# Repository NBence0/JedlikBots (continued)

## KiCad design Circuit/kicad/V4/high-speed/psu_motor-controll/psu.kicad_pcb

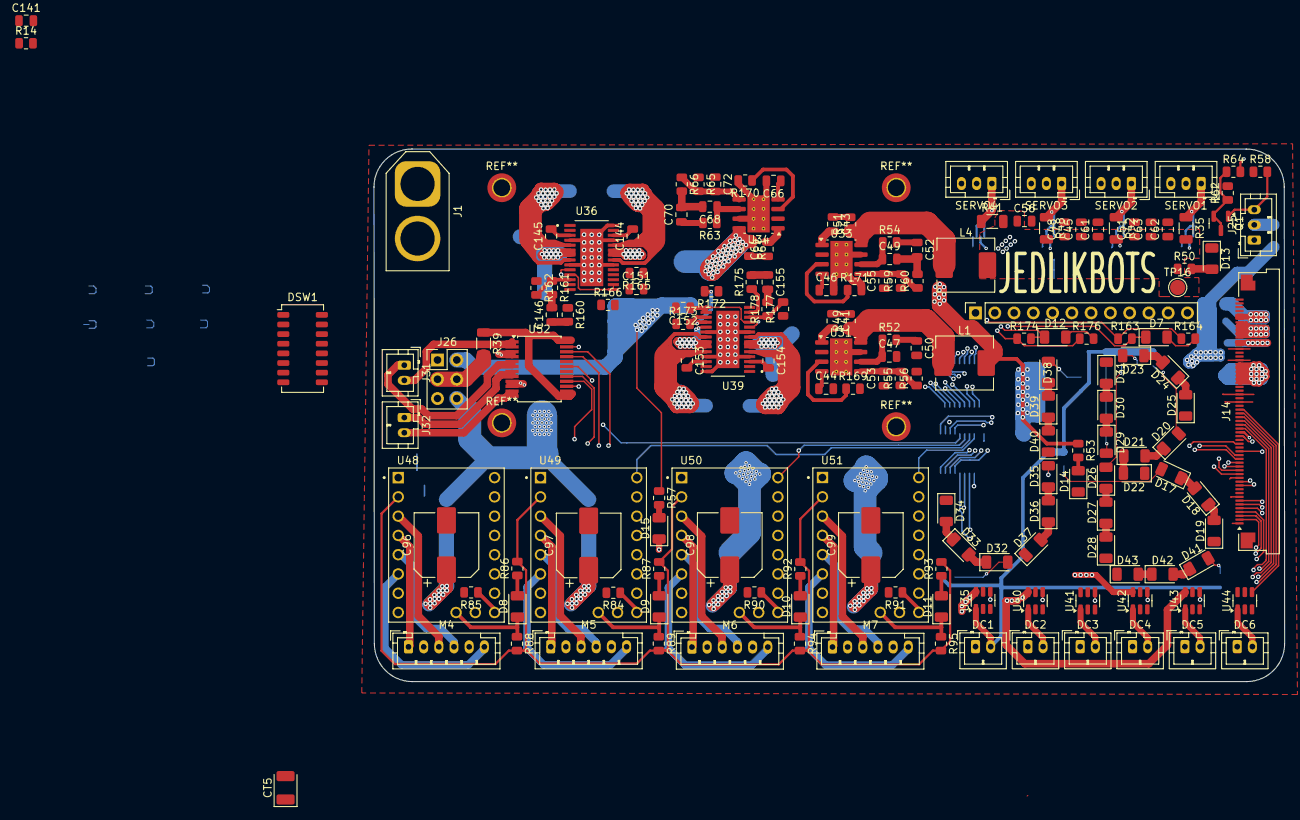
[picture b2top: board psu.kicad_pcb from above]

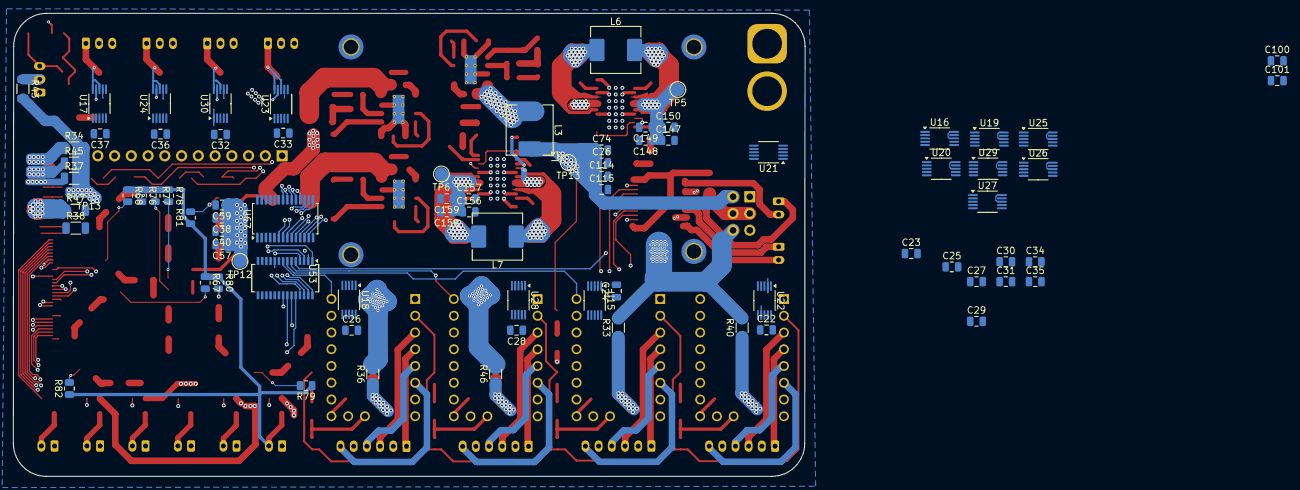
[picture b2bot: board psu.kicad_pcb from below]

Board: 6 copper layers, 120.0 x 70.2 mm, 245 parts (78 on the bottom side), 202 nets.

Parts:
C22, C23, C24, C25, C26, C27, C28, C29, C30, C31, C32, C33, C34, C35, C36, C37, C100, C101, C141: 1uf; C_0805_2012Metric
C38, C40, C45, C48, C51, C56, C57, C59, C61, C62, C63, C74, C76, C114, C115, C147, C148, C149, C150, C151, C152, C156, C157, C158, C159: 4,7uf; C_0805_2012Metric
C41, C43, C44, C46, C64, C66, C144, C145, C153, C154: 100n; C_0805_2012Metric
C47, C49, C53, C55, C68, C72: 68pf; C_0805_2012Metric
C50, C52, C70: 1.2nF; C_0805_2012Metric
C96, C97, C98, C99: 470uf; CP_Elec_8x10
C146, C155: 330pf; C_0805_2012Metric
CT5: 10uf; CP_EIA-3528-21_Kemet-B
D7, D8, D9, D10, D11, D12, D13, D14, D15, D17, D18, D19, D20, D21, D22, D23, D24, D25, D26, D27, D28, D29, D30, D31, D32, D33, D34, D35, D36, D37, D38, D39, D40, D41, D42, D43: LED; D_1206_3216Metric
DC1, DC2, DC3, DC4, DC5, DC6: Conn_01x02_Socket; JST_PH_B2B-PH-K_1x02_P2.00mm_Vertical
DSW1: SW_DIP_x08; SW_DIP_SPSTx08_Slide_Copal_CHS-08A_W5.08mm_P1.27mm_JPin
J1: XT60-M; AMASS_XT60-M_1x02_P7.20mm_Vertical
J14: Conn_01x60_MountingPin; Amphenol_F32Q-1A7x1-11060_1x60-1MP_P0.5mm_Horizontal
J16: Conn_01x12; PinSocket_1x12_P2.54mm_Vertical
J25: Conn_01x03_Pin; JST_PH_B3B-PH-K_1x03_P2.00mm_Vertical
J26: Conn_02x03_Counter_Clockwise; PinHeader_2x03_P2.54mm_Vertical
J31, J32: Conn_01x02_Pin; JST_PH_B2B-PH-K_1x02_P2.00mm_Vertical
L1, L3, L4, L6, L7: HCM0703-3R3-R; L_KOHERelec_MDA7030
M4, M5, M6, M7: Stepper_Motor_unipolar_6pin; JST_PH_B6B-PH-K_1x06_P2.00mm_Vertical
Q1: bss138; SOT-23
R14, R84, R85, R88, R89, R90, R91, R94, R95, R163, R174: 10k; R_0805_2012Metric
R33, R34, R35, R36, R37, R38, R39, R40, R41, R42, R43, R45, R46, R47, R48: 0.025Ω; R_1206_3216Metric
R49, R51, R61: 10R; R_0805_2012Metric
R50: 1k; R_0805_2012Metric
R52, R54, R63: 12K 1%; R_0805_2012Metric
R53: 100; R_0805_2012Metric
R55: 105k; R_0805_2012Metric
R56, R60, R66: 33k; R_0805_2012Metric
R57, R86, R87, R92, R93: 330; R_0805_2012Metric
R58, R62, R64: 100R; R_0805_2012Metric
R59: 210k; R_0805_2012Metric
R65: 178k; R_0805_2012Metric
R67, R68, R76, R77, R78, R79, R80, R81, R82: R_LED; R_0805_2012Metric
R160, R175: 154k; R_0805_2012Metric
R161, R178: 36k; R_0805_2012Metric
R162, R177: 510k; R_0805_2012Metric
R164, R176: 2,2k; R_0805_2012Metric
R165, R173: 34,8k; R_0805_2012Metric
R166, R169, R170, R171, R172: 47k; R_0805_2012Metric
SERVO1, SERVO2, SERVO3, SERVO4: Conn_01x03_Socket; JST_PH_B3B-PH-K_1x03_P2.00mm_Vertical
TP5, TP6, TP12, TP13, TP16: TestPoint; TestPoint_Pad_D2.0mm
U15, U16, U17, U18, U19, U20, U21, U22, U23, U24, U25, U26, U27, U28, U29, U30: INA226; VSSOP-10_3x3mm_P0.5mm
U31, U33, U34: AP64501SP-13; SOIC-8-1EP_3.9x4.9mm_P1.27mm_EP2.95x4.9mm_Mask2.71x3.4mm_Th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
U35, U40, U41, U42, U43, U44: AP22815AWU; SOT-23-6
U36, U39: LTC3119EFE_PBF; SOP65P640X120-29N
U48, U49, U50, U51: TMC2240_SILENTSTEPSTICK; TMC2209
U52: TB6612FNG; SSOP-24_5.3x8.2mm_P0.65mm
U53: MCP23S17_SO; SSOP-28_3.9x9.9mm_P0.635mm
U67: PCA9685PW; TSSOP-28_4.4x9.7mm_P0.65mm

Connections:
3V3_M.2: J14.38, J14.39, J14.40, J14.41, J14.42, J14.43, R47.1, U29.8 (Vbus), U29.10 (Vin+)
3v3: C38.1, C40.1, C53.1, C57.1, C59.1, J26.1, L1.2, R38.2, R47.2, R53.1, R55.1, TP12.1, U20.9 (Vin-), U29.9 (Vin-)
5V1: C22.1, C23.2, C24.1, C25.2, C26.1, C27.2, C28.1, C29.2, C30.1, C31.2, C32.1, C33.2, C34.1, C35.2, C36.1, C37.2, J14.55, J14.56, R34.1, U15.6 (VS), U16.1 (A1), U16.2 (A0), U16.6 (VS), U16.8 (Vbus), U16.10 (Vin+), U17.6 (VS), U18.1 (A1), U18.6 (VS), U19.2 (A0), U19.6 (VS), U20.6 (VS), U21.1 (A1), U21.6 (VS), U22.6 (VS), U23.2 (A0), U23.6 (VS), U24.6 (VS), U25.6 (VS), U26.6 (VS), U27.1 (A1), U27.6 (VS), U28.2 (A0), U28.6 (VS), U29.6 (VS), U30.6 (VS), U41.6 (IN), U44.6 (IN)
5v: C72.1, C74.1, C76.1, C114.1, C115.1, DSW1.7, J26.2, L3.2, R34.2, R37.2, R43.2, R45.2, R57.1, R65.1, TP13.1, U16.9 (Vin-), U19.9 (Vin-), U25.9 (Vin-), U27.9 (Vin-)
/12v_1: C147.1, C148.1, C149.1, C150.1, J26.6, R33.2, R40.2, R162.1, R163.1, R164.1, TP5.1, U15.9 (Vin-), U22.9 (Vin-), U36.6 (PVOUT), U36.7 (PVOUT)
/12v_2: C156.1, C157.1, C158.1, C159.1, R36.2, R46.2, R174.1, R176.1, R177.1, TP6.1, U18.9 (Vin-), U28.9 (Vin-), U39.6 (PVOUT), U39.7 (PVOUT)
/INA226/-1000111: J26.3, J26.4, R39.2, U21.9 (Vin-)
/PSUs/3v3_enable: DSW1.15, R169.1, U31.3 (EN)
/PSUs/5v_enable: DSW1.14, R170.1, U34.3 (EN)
/PSUs/12v_v1_enable: DSW1.12, R166.2, U36.18 (RUN)
/PSUs/12v_v2_enable: DSW1.11, R172.2, U39.18 (RUN)
/PSUs/servo_enable: DSW1.13, R171.1, U33.3 (EN)
/SW_N: DSW1.1, J1.2 (POS)
/SW_P: DSW1.16, J1.1 (NEG)
/YD-ESP32-S3/4x tmc5161/M1_CS: U48.13 (Chip_select), U53.21 (GPA0)
/YD-ESP32-S3/4x tmc5161/M1_EN: R85.1, U48.16 (Enable), U53.1 (GPB0)
/YD-ESP32-S3/4x tmc5161/M2_CS: U50.13 (Chip_select), U53.22 (GPA1)
/YD-ESP32-S3/4x tmc5161/M2_EN: R90.1, U50.16 (Enable), U53.2 (GPB1)
/YD-ESP32-S3/4x tmc5161/M3_CS: U49.13 (Chip_select), U53.23 (GPA2)
/YD-ESP32-S3/4x tmc5161/M3_EN: R84.1, U49.16 (Enable), U53.3 (GPB2)
/YD-ESP32-S3/4x tmc5161/M4_CS: U51.13 (Chip_select), U53.24 (GPA3)
/YD-ESP32-S3/4x tmc5161/M4_EN: R91.1, U51.16 (Enable), U53.4 (GPB3)
/YD-ESP32-S3/H-bridge/AIN1: U52.21 (AIN1), U53.28 (GPA7)
/YD-ESP32-S3/H-bridge/AIN2: U52.22 (AIN2), U53.27 (GPA6)
/YD-ESP32-S3/H-bridge/BIN1: U52.17 (BIN1), U53.26 (GPA5)
/YD-ESP32-S3/H-bridge/BIN2: U52.16 (BIN2), U53.25 (GPA4)
/YD-ESP32-S3/I2C_SCL_sensors: J14.10, U67.27 (SDA)
/YD-ESP32-S3/I2C_SDA_sensors: J14.9, U67.26 (SCL)
/YD-ESP32-S3/I2C_devices/PCA9531PW/SM1_PWM: SERVO1.2, U67.6 (LED0)
/YD-ESP32-S3/I2C_devices/PCA9531PW/SM2_PWM: SERVO2.2, U67.7 (LED1)
/YD-ESP32-S3/I2C_devices/PCA9531PW/SM3_PWM: SERVO3.2, U67.8 (LED2)
/YD-ESP32-S3/I2C_devices/PCA9531PW/SM4_PWM: SERVO4.2, U67.9 (LED3)
/YD-ESP32-S3/M1_dir: U48.9 (DIR), U53.5 (GPB4)
/YD-ESP32-S3/M1_step: J14.17, U48.10 (STEP)
/YD-ESP32-S3/M2_dir: U50.9 (DIR), U53.6 (GPB5)
/YD-ESP32-S3/M2_step: J14.16, U50.10 (STEP)
/YD-ESP32-S3/M3_dir: U49.9 (DIR), U53.7 (GPB6)
/YD-ESP32-S3/M3_step: J14.15, U49.10 (STEP)
/YD-ESP32-S3/M4_dir: U51.9 (DIR), U53.8 (GPB7)
/YD-ESP32-S3/M4_step: J14.14, U51.10 (STEP)
/YD-ESP32-S3/MCP_RST: J14.20, U53.18 (~RESET)
/YD-ESP32-S3/PWMA: J14.19, U52.23 (PWMA)
/YD-ESP32-S3/PWMB: J14.18, U52.15 (PWMB)
/YD-ESP32-S3/SPI_2_CLK: J14.7, U53.12 (SCK)
/YD-ESP32-S3/SPI_2_MISO: J14.5, U53.14 (SO)
/YD-ESP32-S3/SPI_2_MOSI: J14.6, U53.13 (SI)
/YD-ESP32-S3/Shift_registers/JB_leds/+12V: DC1.2, R67.1, R68.1, R76.1, R77.1, R78.1, R79.1, R80.1, R81.1, R82.1, U35.1 (OUT)
/YD-ESP32-S3/TMC_MISO: J14.2, U48.11 (MISO), U49.11 (MISO), U50.11 (MISO), U51.11 (MISO)
/YD-ESP32-S3/TMC_MOSI: J14.4, U48.15 (MOSI), U49.15 (MOSI), U50.15 (MOSI), U51.15 (MOSI)
/YD-ESP32-S3/TMC_SPI_CLK: J14.3, U48.14 (Spi_clk), U49.14 (Spi_clk), U50.14 (Spi_clk), U51.14 (Spi_clk)
/servo: C45.1, C48.1, C51.1, C55.1, C56.1, C61.1, C62.1, C63.1, J26.5, L4.2, R35.2, R41.2, R42.2, R48.2, R50.1, R59.1, TP16.1, U17.9 (Vin-), U23.9 (Vin-), U24.9 (Vin-), U30.9 (Vin-)
B-B_2: J14.31, U44.4 (EN)
B-B_3: J14.30, U43.4 (EN)
B-B_4: J14.29, U42.4 (EN)
B-B_5: J14.28, U41.4 (EN)
B-B_6: J14.27, U40.4 (EN)
B-B_7: J14.26, U35.4 (EN)
ESP_3v3: C100.1, C101.1, C141.1, CT5.1, J14.36, J14.37, R38.1, R62.2, R86.2, R87.2, R88.2, R89.2, R92.2, R93.2, R94.2, R95.2, U20.8 (Vbus), U20.10 (Vin+), U40.6 (IN), U43.6 (IN), U48.2 (VIO/VDD), U49.2 (VIO/VDD), U50.2 (VIO/VDD), U51.2 (VIO/VDD), U52.20 (VCC), U53.9 (VDD), U67.2 (A1), U67.5 (A4), U67.24 (A5), U67.28 (VDD)
ESP_5v: J14.48, J14.49, R37.1, R58.1, U19.8 (Vbus), U19.10 (Vin+)
GND: C22.2, C23.1, C24.2, C25.1, C26.2, C27.1, C28.2, C29.1, C30.2, C31.1, C32.2, C33.1, C34.2, C35.1, C36.2, C37.1, C38.2, C40.2, C44.2, C45.2, C46.2, C47.2, C48.2, C49.2, C50.2, C51.2, C52.2, C56.2, C57.2, C59.2, C61.2, C62.2, C63.2, C66.2, C68.2, C70.2, C74.2, C76.2, C96.2, C97.2, C98.2, C99.2, C100.2, C101.2, C114.2, C115.2, C141.2, C147.2, C148.2, C149.2, C150.2, C151.2, C152.2, C156.2, C157.2, C158.2, C159.2, CT5.2, D13.1 (K), D14.1 (K), D15.1 (K), D19.1 (K), D22.1 (K), D25.1 (K), D28.1 (K), D31.1 (K), D34.1 (K), D37.1 (K), D40.1 (K), D43.1 (K), DC1.1, DC2.1, DC3.1, DC4.1, DC5.1, DC6.1, DSW1.9, J14.1, J14.8, J14.13, J14.33, J14.34, J14.35, J14.44, J14.45, J14.46, J14.47, J14.57, J14.58, J14.59, J14.60, J14.MP (MountPin), J25.1, R14.2, R56.2, R60.2, R66.2, R84.2, R85.2, R90.2, R91.2, R165.1, R166.1, R169.2, R170.2, R171.2, R172.1, R173.1, SERVO1.3, SERVO2.3, SERVO3.3, SERVO4.3, U15.1 (A1), U15.2 (A0), U15.7 (GND), U16.7 (GND), U17.7 (GND), U18.2 (A0), U18.7 (GND), U19.7 (GND), U20.7 (GND), U21.7 (GND), U22.2 (A0), U22.7 (GND), U23.7 (GND), U24.7 (GND), U25.2 (A0), U25.7 (GND), U26.1 (A1), U26.7 (GND), U27.7 (GND), U28.1 (A1), U28.7 (GND), U29.7 (GND), U30.1 (A1), U30.7 (GND), U31.7 (GND), U31.9 (EP), U33.7 (GND), U33.9 (EP), U34.7 (GND), U34.9 (EP), U35.2 (GND), U36.4 (PGND), U36.9 (PGND), U36.14 (SGND), U36.20 (PGND), U36.25 (PGND), U36.28 (PWM/SYNC), U36.29 (PGND), U39.4 (PGND), U39.9 (PGND), U39.14 (SGND), U39.20 (PGND), U39.25 (PGND), U39.28 (PWM/SYNC), U39.29 (PGND), U40.2 (GND), U41.2 (GND), U42.2 (GND), U43.2 (GND), U44.2 (GND), U48.1 (GND), U48.7 (GND), U49.1 (GND), U49.7 (GND), U50.1 (GND), U50.7 (GND), U51.1 (GND), U51.7 (GND), U52.3 (PGND1), U52.4 (PGND1), U52.9 (PGND2), U52.10 (PGND2), U52.18 (GND), U53.10 (VSS), U53.15 (A0), U53.16 (A1), U53.17 (A2), U67.1 (A0), U67.3 (A2), U67.4 (A3), U67.14 (VSS)
H-bridge: R39.1, U21.8 (Vbus), U21.10 (Vin+), U52.13 (VM2), U52.14 (VM3), U52.24 (VM1)
H_EN: J14.22, U52.19 (STBY)
I2C_RST: J14.21, R14.1, U67.23 (~OE)
INA226_ALERT: J14.32, U15.3 (~Alert), U16.3 (~Alert), U17.3 (~Alert), U18.3 (~Alert), U19.3 (~Alert), U20.3 (~Alert), U21.3 (~Alert), U22.3 (~Alert), U23.3 (~Alert), U24.3 (~Alert), U25.3 (~Alert), U26.3 (~Alert), U27.3 (~Alert), U28.3 (~Alert), U29.3 (~Alert), U30.3 (~Alert)
INA226_SCL: J14.12, U15.4 (SDA), U16.4 (SDA), U17.4 (SDA), U18.4 (SDA), U19.4 (SDA), U20.1 (A1), U20.4 (SDA), U21.2 (A0), U21.4 (SDA), U22.4 (SDA), U23.1 (A1), U23.4 (SDA), U24.2 (A0), U24.4 (SDA), U25.1 (A1), U25.4 (SDA), U26.4 (SDA), U27.4 (SDA), U28.4 (SDA), U29.1 (A1), U29.2 (A0), U29.4 (SDA), U30.2 (A0), U30.4 (SDA)
INA226_SDA: J14.11, U15.5 (SCL), U16.5 (SCL), U17.1 (A1), U17.2 (A0), U17.5 (SCL), U18.5 (SCL), U19.1 (A1), U19.5 (SCL), U20.2 (A0), U20.5 (SCL), U21.5 (SCL), U22.1 (A1), U22.5 (SCL), U23.5 (SCL), U24.1 (A1), U24.5 (SCL), U25.5 (SCL), U26.2 (A0), U26.5 (SCL), U27.2 (A0), U27.5 (SCL), U28.5 (SCL), U29.5 (SCL), U30.5 (SCL)
INPUT_VOLTAGE: DSW1.2, DSW1.3, DSW1.4, DSW1.5, DSW1.6, U26.8 (Vbus), U26.10 (Vin+), U31.2 (VIN), U33.2 (VIN), U34.2 (VIN), U36.19 (VIN), U36.22 (PVIN), U36.23 (PVIN), U39.19 (VIN), U39.22 (PVIN), U39.23 (PVIN)
MCP_CS: J14.24, U53.11 (~CS)
Motor 1 power: C96.1, R40.1, U22.8 (Vbus), U22.10 (Vin+), U35.6 (IN), U48.8 (VMOT)
Motor 2 power: C98.1, R46.1, U28.8 (Vbus), U28.10 (Vin+), U42.6 (IN), U50.8 (VMOT)
Motor 3 power: C97.1, R33.1, U15.8 (Vbus), U15.10 (Vin+), U49.8 (VMOT)
Motor 4 power: C99.1, R36.1, U18.8 (Vbus), U18.10 (Vin+), U51.8 (VMOT)
unnamed: C41.1, R49.2
unnamed: C43.1, R51.2
unnamed: C50.1, R52.2
unnamed: C52.1, R54.2
unnamed: C64.1, R61.2
unnamed: C70.1, R63.2
unnamed: C144.1, L6.1, U36.21 (SW1), U36.24 (SW1)
unnamed: C145.1, L6.2, U36.5 (SW2), U36.8 (SW2)
unnamed: C146.1, R160.2
unnamed: C146.2, R161.2
unnamed: C153.1, L7.1, U39.21 (SW1), U39.24 (SW1)
unnamed: C154.1, L7.2, U39.5 (SW2), U39.8 (SW2)
unnamed: C155.1, R175.2
unnamed: C155.2, R178.2
unnamed: D7.2 (A), R164.2
unnamed: D7.1 (K), R163.2, U36.10 (PGOOD)
unnamed: D8.2 (A), R86.1
unnamed: D8.1 (K), R88.1, U48.17 (DIAG)
unnamed: D9.2 (A), R87.1
unnamed: D9.1 (K), R89.1, U49.17 (DIAG)
unnamed: D10.2 (A), R92.1
unnamed: D10.1 (K), R94.1, U50.17 (DIAG)
unnamed: D11.2 (A), R93.1
unnamed: D11.1 (K), R95.1, U51.17 (DIAG)
unnamed: D12.2 (A), R176.2
unnamed: D12.1 (K), R174.2, U39.10 (PGOOD)
unnamed: D13.2 (A), R50.2
unnamed: D14.2 (A), R53.2
unnamed: D15.2 (A), R57.2
unnamed: D17.2 (A), R67.2
unnamed: D17.1 (K), D18.2 (A)
unnamed: D18.1 (K), D19.2 (A)
unnamed: D20.2 (A), R68.2
unnamed: D20.1 (K), D21.2 (A)
unnamed: D21.1 (K), D22.2 (A)
unnamed: D23.2 (A), R76.2
unnamed: D23.1 (K), D24.2 (A)
unnamed: D24.1 (K), D25.2 (A)
unnamed: D26.2 (A), R77.2
unnamed: D26.1 (K), D27.2 (A)
unnamed: D27.1 (K), D28.2 (A)
unnamed: D29.2 (A), R78.2
unnamed: D29.1 (K), D30.2 (A)
unnamed: D30.1 (K), D31.2 (A)
unnamed: D32.2 (A), R79.2
unnamed: D32.1 (K), D33.2 (A)
unnamed: D33.1 (K), D34.2 (A)
unnamed: D35.2 (A), R80.2
unnamed: D35.1 (K), D36.2 (A)
unnamed: D36.1 (K), D37.2 (A)
unnamed: D38.2 (A), R81.2
unnamed: D38.1 (K), D39.2 (A)
unnamed: D39.1 (K), D40.2 (A)
unnamed: D41.2 (A), R82.2
unnamed: D41.1 (K), D42.2 (A)
unnamed: D42.1 (K), D43.2 (A)
unnamed: DC2.2, U40.1 (OUT)
unnamed: DC3.2, U41.1 (OUT)
unnamed: DC4.2, U42.1 (OUT)
unnamed: DC5.2, U43.1 (OUT)
unnamed: DC6.2, U44.1 (OUT)
unnamed: J16.1, U67.10 (LED4)
unnamed: J16.2, U67.11 (LED5)
unnamed: J16.3, U67.12 (LED6)
unnamed: J16.4, U67.13 (LED7)
unnamed: J16.5, U67.15 (LED8)
unnamed: J16.6, U67.16 (LED9)
unnamed: J16.7, U67.17 (LED10)
unnamed: J16.8, U67.18 (LED11)
unnamed: J16.9, U67.19 (LED12)
unnamed: J16.10, U67.20 (LED13)
unnamed: J16.11, U67.21 (LED14)
unnamed: J16.12, U67.22 (LED15)
unnamed: J25.3, Q1.1 (D), R58.2
unnamed: J31.1, U52.5 (AO2), U52.6 (AO2)
unnamed: J31.2, U52.1 (AO1), U52.2 (AO1)
unnamed: J32.1, U52.7 (BO2), U52.8 (BO2)
unnamed: J32.2, U52.11 (BO1), U52.12 (BO1)
unnamed: M4.3 (-), U48.3 (M1B)
unnamed: M5.3 (-), U49.3 (M1B)
unnamed: M6.3 (-), U50.3 (M1B)
unnamed: M7.3 (-), U51.3 (M1B)
unnamed: Q1.2 (G), Q1.3 (S), R62.1, R64.1
unnamed: C41.2, U31.1 (BST)
unnamed: C47.1, R52.1, U31.6 (COMP)
unnamed: C53.2, R55.2, R56.1, U31.5 (FB)
unnamed: C44.1, U31.4 (SS)
unnamed: L1.1, R49.1, U31.8 (SW)
unnamed: C43.2, U33.1 (BST)
unnamed: C49.1, R54.1, U33.6 (COMP)
unnamed: C55.2, R59.2, R60.1, U33.5 (FB)
unnamed: C46.1, U33.4 (SS)
unnamed: L4.1, R51.1, U33.8 (SW)
unnamed: C64.2, U34.1 (BST)
unnamed: C68.1, R63.1, U34.6 (COMP)
unnamed: C72.2, R65.2, R66.1, U34.5 (FB)
unnamed: C66.1, U34.4 (SS)
unnamed: L3.1, R61.1, U34.8 (SW)
unnamed: C144.2, U36.26 (BST1)
unnamed: C145.2, U36.3 (BST2)
unnamed: R161.1, R162.2, U36.12 (FB)
unnamed: C151.1, U36.11 (SVCC), U36.15 (MPPC), U36.16 (VCC)
unnamed: R165.2, U36.17 (RT)
unnamed: R160.1, U36.13 (VC)
unnamed: C153.2, U39.26 (BST1)
unnamed: C154.2, U39.3 (BST2)
unnamed: R177.2, R178.1, U39.12 (FB)
unnamed: C152.1, U39.11 (SVCC), U39.15 (MPPC), U39.16 (VCC)
unnamed: R173.2, U39.17 (RT)
unnamed: R175.1, U39.13 (VC)
unnamed: M4.6, U48.6 (M1A)
unnamed: M4.4, U48.5 (M2A)
unnamed: M4.1, U48.4 (M2B)
unnamed: M5.6, U49.6 (M1A)
unnamed: M5.4, U49.5 (M2A)
unnamed: M5.1, U49.4 (M2B)
unnamed: M6.6, U50.6 (M1A)
unnamed: M6.4, U50.5 (M2A)
unnamed: M6.1, U50.4 (M2B)
unnamed: M7.6, U51.6 (M1A)
unnamed: M7.4, U51.5 (M2A)
unnamed: M7.1, U51.4 (M2B)
RPI_5V: J14.50, J14.51, J14.52, J14.53, J14.54, R45.1, U27.8 (Vbus), U27.10 (Vin+)
SERVO1: R35.1, SERVO1.1, U17.8 (Vbus), U17.10 (Vin+)
SERVO2: R42.1, SERVO2.1, U24.8 (Vbus), U24.10 (Vin+)
SERVO3: R48.1, SERVO3.1, U30.8 (Vbus), U30.10 (Vin+)
SERVO4: R41.1, SERVO4.1, U23.8 (Vbus), U23.10 (Vin+)
TPA_ON: DSW1.10, J14.23
WS_2802B_DATA: J14.25, R64.2
WS_2802B_POWER: J25.2, R43.1, U25.8 (Vbus), U25.10 (Vin+)
